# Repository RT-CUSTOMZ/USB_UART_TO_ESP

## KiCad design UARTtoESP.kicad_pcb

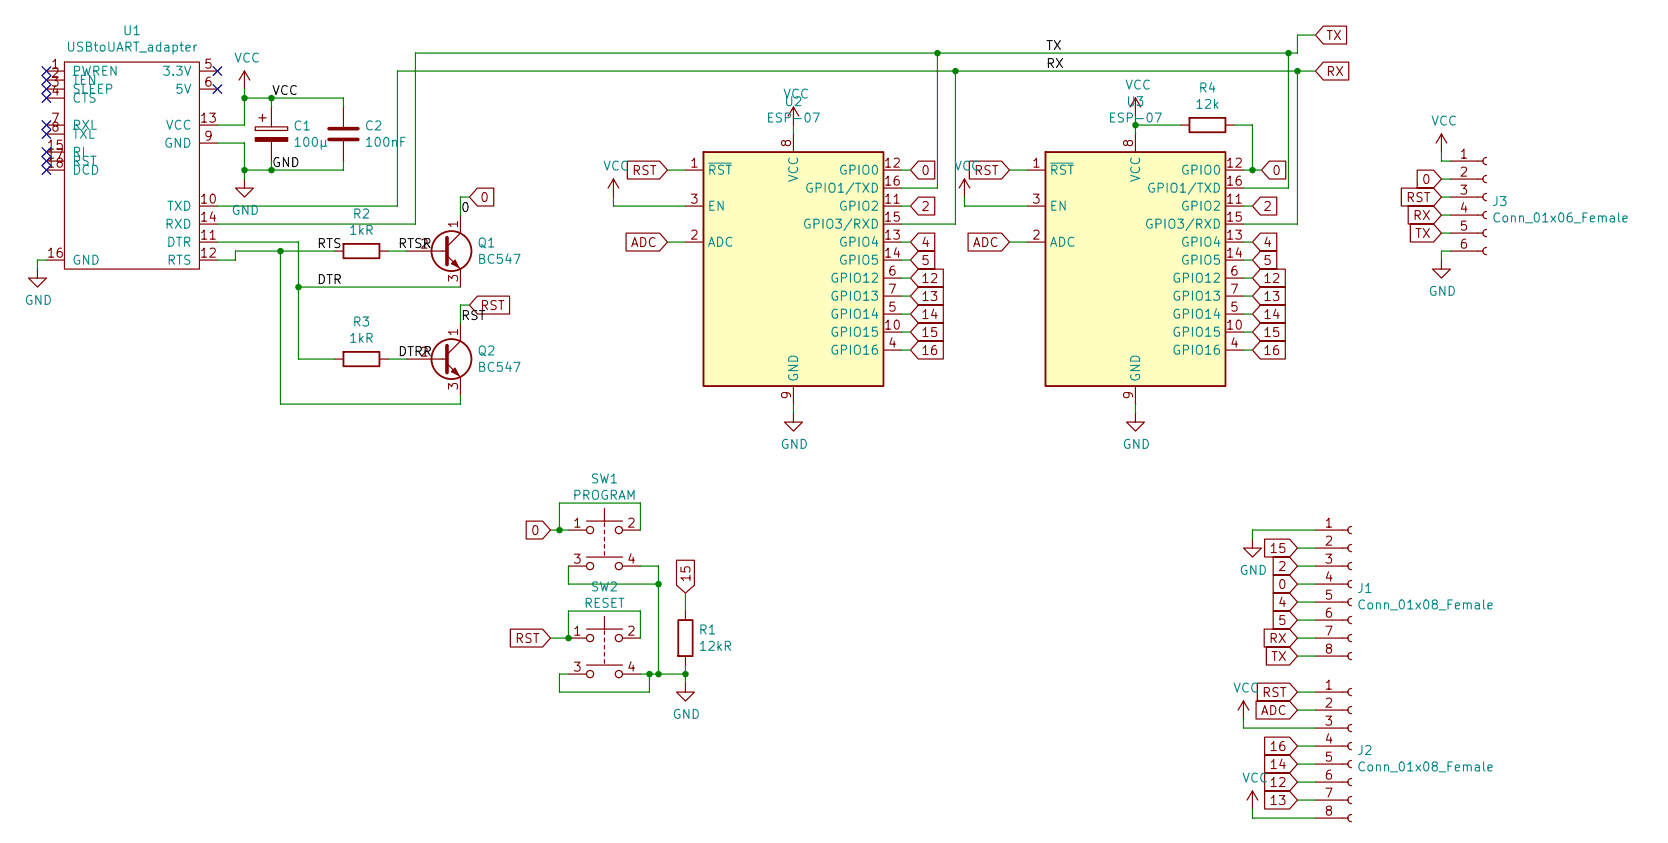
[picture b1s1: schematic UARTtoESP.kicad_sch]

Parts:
C1: 100µ; CP_Radial_D10.0mm_P5.00mm
C2: 100nF; C_Rect_L7.0mm_W2.0mm_P5.00mm
J1, J2: Conn_01x08_Female; PinHeader_1x08_P2.54mm_Vertical
J3: Conn_01x06_Female; PinHeader_1x06_P2.54mm_Vertical
Q1, Q2: BC547; TO-92_Inline
R1: 12kR; R_Axial_DIN0207_L6.3mm_D2.5mm_P10.16mm_Horizontal
R2, R3: 1kR; R_Axial_DIN0207_L6.3mm_D2.5mm_P10.16mm_Horizontal
R4: 12k; R_Axial_DIN0207_L6.3mm_D2.5mm_P10.16mm_Horizontal
SW1: PROGRAM; SW_TH_Tactile_Omron_B3F-10xx
SW2: RESET; SW_TH_Tactile_Omron_B3F-10xx
U1: USBtoUART_adapter; USBtoUART_USBtoTTL_FT232rl
U2, U3: ESP-07; ESP-07_tht

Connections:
0: J1.4, J3.2, Q1.1 (C), R4.1, SW1.1, SW1.2, U2.12 (GPIO0), U3.12 (GPIO0)
2: J1.3, U2.11 (GPIO2), U3.11 (GPIO2)
4: J1.5, U2.13 (GPIO4), U3.13 (GPIO4)
5: J1.6, U2.14 (GPIO5), U3.14 (GPIO5)
12: J2.6, U2.6 (GPIO12), U3.6 (GPIO12)
13: J2.7, U2.7 (GPIO13), U3.7 (GPIO13)
14: J2.5, U2.5 (GPIO14), U3.5 (GPIO14)
15: J1.2, R1.1, U2.10 (GPIO15), U3.10 (GPIO15)
16: J2.4, U2.4 (GPIO16), U3.4 (GPIO16)
/DTR: Q1.3 (E), R3.2, U1.11 (DTR)
/DTRR: Q2.2 (B), R3.1
/RTS: Q2.3 (E), R2.2, U1.12 (RTS)
/RTSR: Q1.2 (B), R2.1
ADC: J2.2, U2.2 (ADC), U3.2 (ADC)
GND: C1.2, C2.2, J1.1, J3.6, R1.2, SW1.3, SW1.4, SW2.3, SW2.4, U1.9 (GND), U1.16 (GND), U2.9 (GND), U3.9 (GND)
RST: J2.1, J3.3, Q2.1 (C), SW2.1, SW2.2, U2.1 (~RST), U3.1 (~RST)
RX: J1.7, J3.4, U1.10 (TXD), U2.15 (GPIO3/RXD), U3.15 (GPIO3/RXD)
TX: J1.8, J3.5, U1.14 (RXD), U2.16 (GPIO1/TXD), U3.16 (GPIO1/TXD)
VCC: C1.1, C2.1, J2.3, J2.8, J3.1, R4.2, U1.13 (VCC), U2.3 (EN), U2.8 (VCC), U3.3 (EN), U3.8 (VCC)

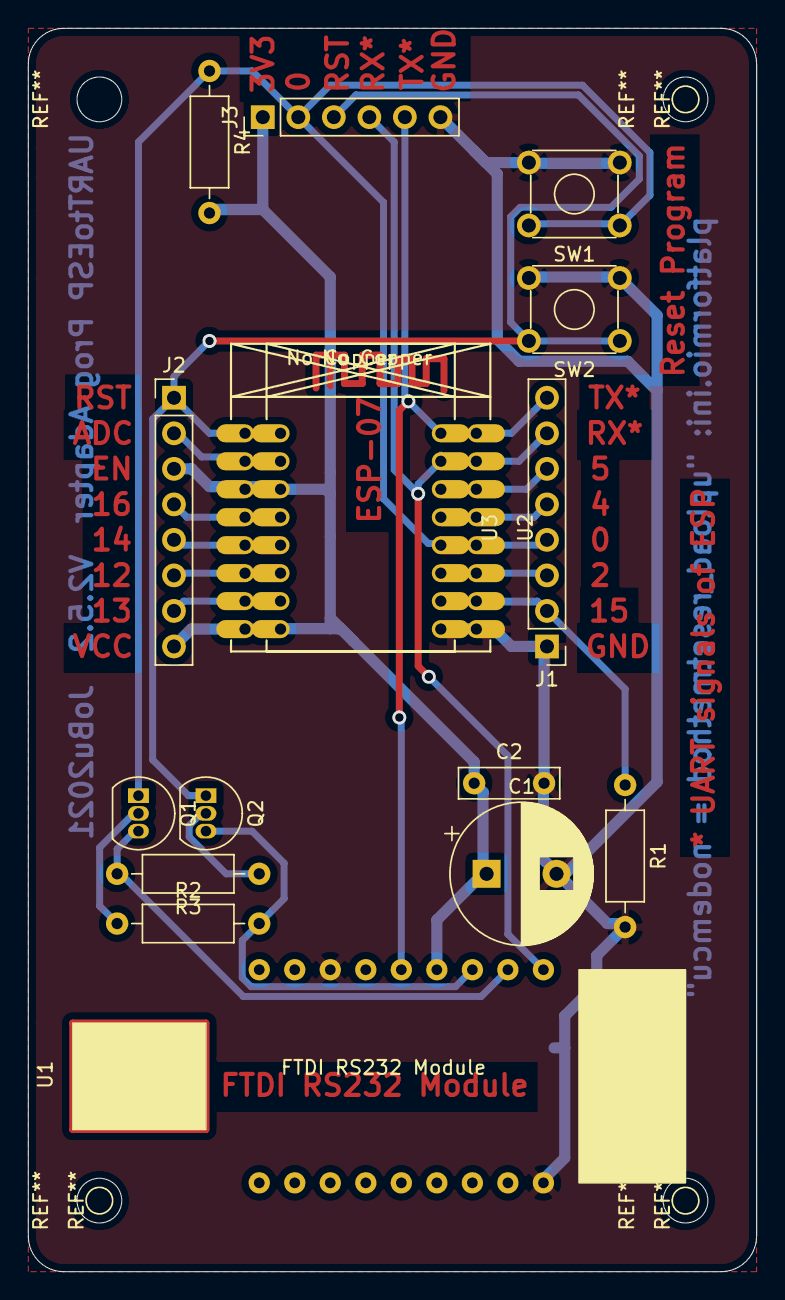
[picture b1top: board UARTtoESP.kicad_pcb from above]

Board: 2 copper layers, 52.1 x 88.9 mm, 16 parts (0 on the bottom side), 19 nets.
